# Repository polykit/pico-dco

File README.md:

# Raspberry Pi Pico Polyphonic DCO

This repository contains source code, schematics and PCB for a digitally controlled oscillator (DCO) with up to 6 voices which are driven by a Raspberry Pi Pico. It uses PIO to generate a highly accurate frequency which is controlled by USB or serial MIDI. The analog oscillator part is based on the Juno 106 and generates sawtooth and square wave signal with a 10Vpp amplitude. Amplitude compensation is done by a smoothed PWM signal coming from the Pico.

## Key features

- Digitally controlled analog oscillator using a Raspberry Pi Pico
- Up to six voices
- Voice stacking
- Detuning of voices
- Frequency modulation (FM)
- Separate gate signal
- DIN MIDI serial input
- USB MIDI input
- MIDI pitch bend
- Portamento with adjustable speed

This is how it sounds: [Ramp sample](https://soundcloud.com/polykit/pico-dco-ramp) [Pulse sample](https://soundcloud.com/polykit/pico-dco-pulse) [Polyphonic sample](https://soundcloud.com/polykit/pico-dco-polyphonic)

I use the DCO in my Polykit-6 polyphonic synthesizer, see https://www.youtube.com/watch?v=vj-DSh6yfM0 and https://www.youtube.com/watch?v=go1mErOdtsU

## Schematics and PCB

Gerber files for the PCB can be found [here](kicad/plots).

## Installation (simple)

Press `BOOTSEL` button on the Pico while powering it with USB. Copy file `build/pico-dco.uf2` onto the USB mass storage device.

## Usage

After installing the Pico should register as USB MIDI device. Alternatively serial MIDI input is available. The DCO listens to note on/note off messages on MIDI channel 1. Pitch bend is also supported. Portamento can be enabled by MIDI CC message #65, portamento time can be adjusted by CC message #5.

## Detuning, stacking and FM

The build-in analog-to-digital converter can be used to modulate these parameters. You can add an external control voltage (0-3.3V) to that input pins. These features can be disabled by commenting (`//`) the following lines:

```
#define USE_ADC_STACK_VOICES // gpio 28 (adc 2)
#define USE_ADC_DETUNE       // gpio 27 (adc 1)
#define USE_ADC_FM           // gpio 26 (adc 0)
```

## References

https://blog.thea.codes/the-design-of-the-juno-dco/

https://electricdruid.net/roland-juno-dcos/

https://www.youtube.com/watch?v=yYnQYF_Xa8g

https://github.com/raspberrypi/pico-examples/tree/master/pio/pwm

https://github.com/raspberrypi/pico-examples/tree/master/pio/pio_blink

https://github.com/raspberrypi/pico-examples/tree/master/pwm/hello_pwm

https://qiita.com/jamjam/items/f2fdd5c072ff348fd809

https://github.com/infovore/pico-example-midi

https://learn.sparkfun.com/tutorials/midi-tutorial/all

http://www.music-software-development.com/midi-tutorial.html

http://midi.teragonaudio.com/tech/midispec/run.htm

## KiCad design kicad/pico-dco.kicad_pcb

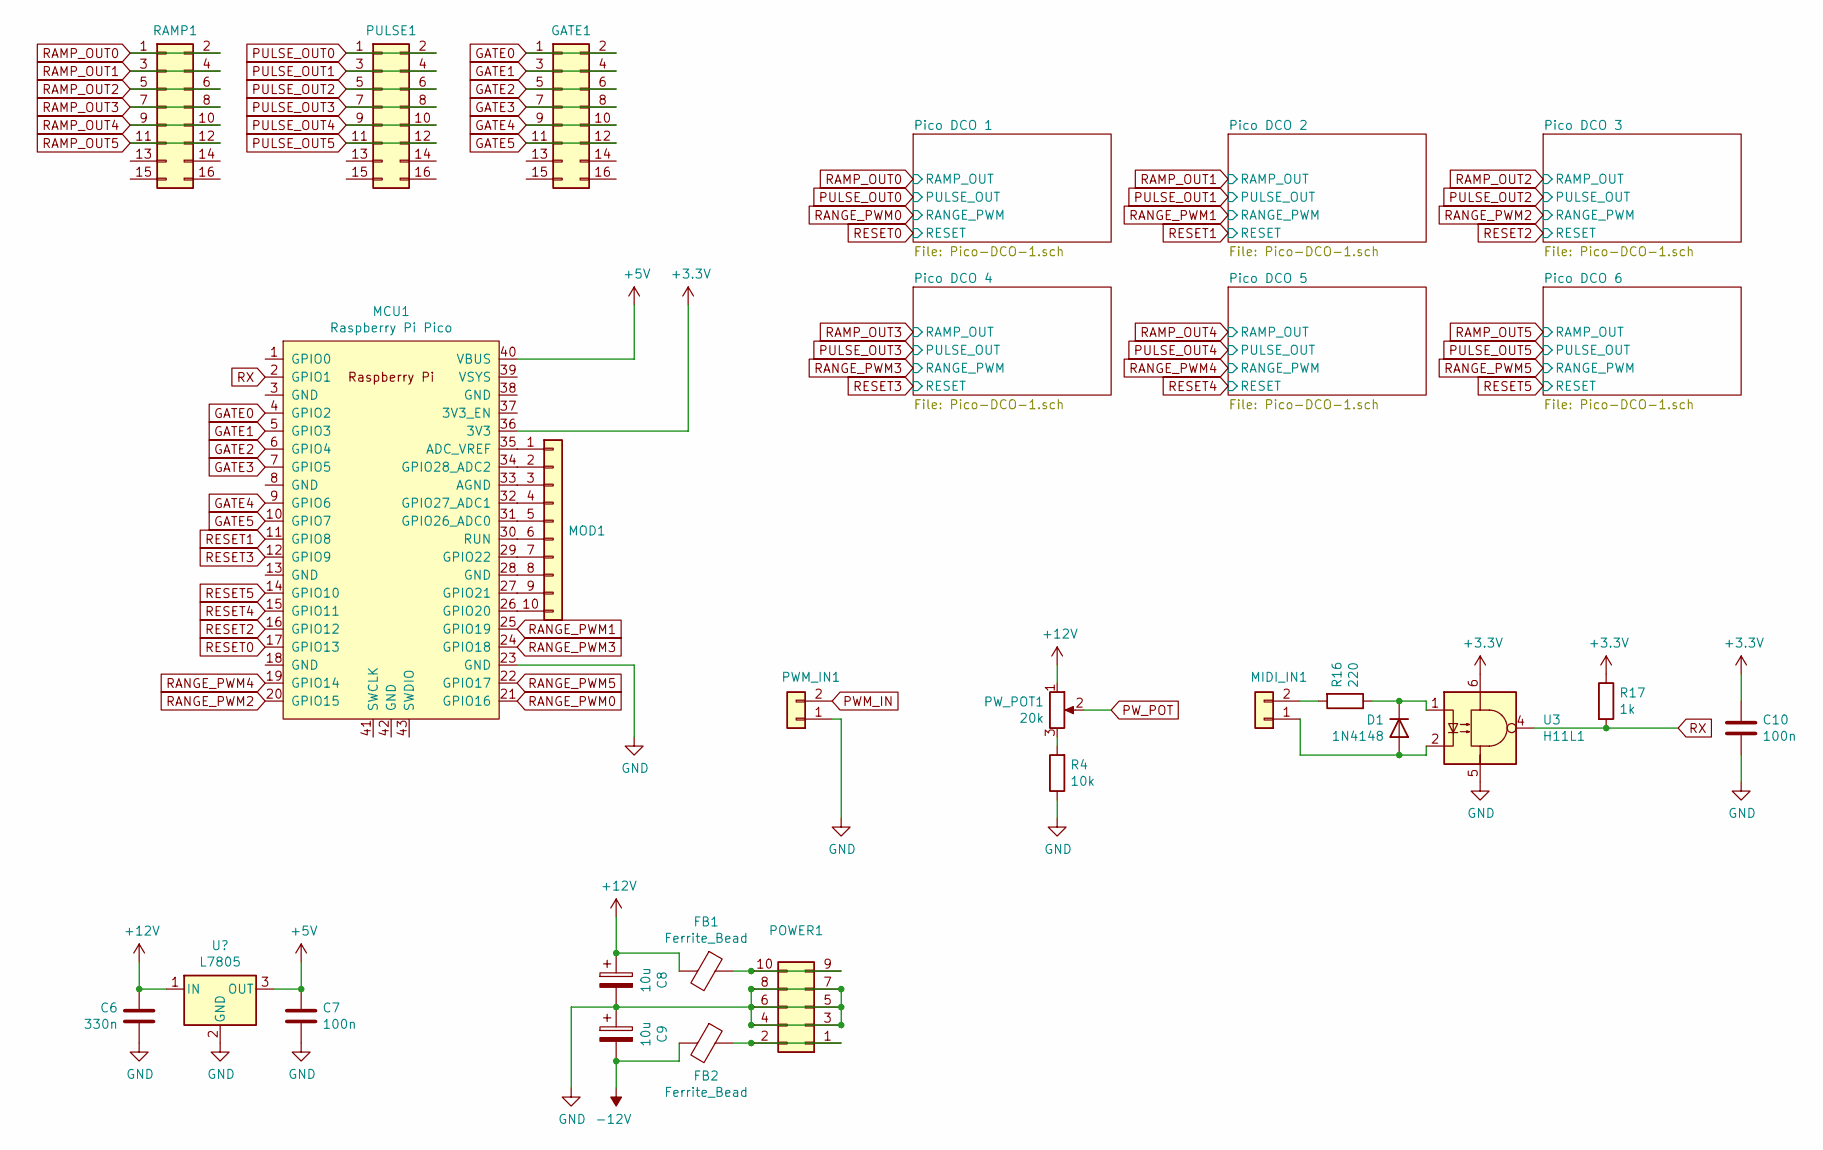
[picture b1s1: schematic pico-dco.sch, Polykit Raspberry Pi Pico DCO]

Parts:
C6: 330n; C_Rect_L7.2mm_W4.5mm_P5.00mm_FKS2_FKP2_MKS2_MKP2
C7, C10: 100n; C_Rect_L7.2mm_W4.5mm_P5.00mm_FKS2_FKP2_MKS2_MKP2
C8, C9: 10u; CP_Radial_D5.0mm_P2.00mm
D1: 1N4148; D_DO-35_SOD27_P7.62mm_Horizontal
FB1, FB2: Ferrite_Bead; R_Axial_DIN0207_L6.3mm_D2.5mm_P10.16mm_Horizontal
GATE1: Conn_02x08_Odd_Even; IDC-Header_2x08_P2.54mm_Vertical
MCU1: Raspberry Pi Pico; RPi_Pico_SMD_TH
MIDI_IN1: Conn_01x02; Molex_KK-254_AE-6410-02A_1x02_P2.54mm_Vertical
MOD1: Conn_01x10; PinHeader_1x10_P2.54mm_Vertical
POWER1: Conn_02x05_Odd_Even; IDC-Header_2x05_P2.54mm_Vertical
PULSE1: Conn_02x08_Odd_Even; IDC-Header_2x08_P2.54mm_Vertical
PWM_IN1: Conn_01x02; Molex_KK-254_AE-6410-02A_1x02_P2.54mm_Vertical
PW_POT1: 20k; Molex_KK-254_AE-6410-03A_1x03_P2.54mm_Vertical
R4: 10k; R_Axial_DIN0207_L6.3mm_D2.5mm_P10.16mm_Horizontal
R16: 220; R_Axial_DIN0207_L6.3mm_D2.5mm_P10.16mm_Horizontal
R17: 1k; R_Axial_DIN0207_L6.3mm_D2.5mm_P10.16mm_Horizontal
RAMP1: Conn_02x08_Odd_Even; IDC-Header_2x08_P2.54mm_Vertical
U3: H11L1; DIP-6_W7.62mm_Socket_LongPads

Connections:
+3V3: C10.1, MCU1.36 (3V3), R17.1, U3.6
+5V: C7.1, MCU1.40 (VBUS); also elsewhere on the board
+12V: C6.2, C8.1, FB1.2, PW_POT1.1; also elsewhere on the board
-12V: C9.2, FB2.2; also elsewhere on the board
GATE0: GATE1.1, GATE1.2, MCU1.4 (GPIO2)
GATE1: GATE1.3, GATE1.4, MCU1.5 (GPIO3)
GATE2: GATE1.5, GATE1.6, MCU1.6 (GPIO4)
GATE3: GATE1.7, GATE1.8, MCU1.7 (GPIO5)
GATE4: GATE1.9, GATE1.10, MCU1.9 (GPIO6)
GATE5: GATE1.11, GATE1.12, MCU1.10 (GPIO7)
GND: C6.1, C7.2, C8.2, C9.1, C10.2, MCU1.23 (GND), POWER1.3, POWER1.4, POWER1.5, POWER1.6, POWER1.7, POWER1.8, PWM_IN1.1, R4.1, U3.5; also elsewhere on the board
unnamed: D1.1 (K), R16.1, U3.1
unnamed: D1.2 (A), MIDI_IN1.1, U3.2
unnamed: FB1.1, POWER1.9, POWER1.10
unnamed: FB2.1, POWER1.1, POWER1.2
unnamed: MCU1.26 (GPIO20), MOD1.10
unnamed: MCU1.27 (GPIO21), MOD1.9
unnamed: MCU1.28 (GND), MOD1.8
unnamed: MCU1.29 (GPIO22), MOD1.7
unnamed: MCU1.30 (RUN), MOD1.6
unnamed: MCU1.31 (GPIO26_ADC0), MOD1.5
unnamed: MCU1.32 (GPIO27_ADC1), MOD1.4
unnamed: MCU1.33 (AGND), MOD1.3
unnamed: MCU1.34 (GPIO28_ADC2), MOD1.2
unnamed: MCU1.35 (ADC_VREF), MOD1.1
unnamed: MIDI_IN1.2, R16.2
unnamed: PW_POT1.3, R4.2
PULSE_OUT0: PULSE1.1, PULSE1.2; also elsewhere on the board
PULSE_OUT1: PULSE1.3, PULSE1.4; also elsewhere on the board
PULSE_OUT2: PULSE1.5, PULSE1.6; also elsewhere on the board
PULSE_OUT3: PULSE1.7, PULSE1.8; also elsewhere on the board
PULSE_OUT4: PULSE1.9, PULSE1.10; also elsewhere on the board
PULSE_OUT5: PULSE1.11, PULSE1.12; also elsewhere on the board
PWM_IN: PWM_IN1.2; also elsewhere on the board
PW_POT: PW_POT1.2; also elsewhere on the board
RAMP_OUT0: RAMP1.1, RAMP1.2; also elsewhere on the board
RAMP_OUT1: RAMP1.3, RAMP1.4; also elsewhere on the board
RAMP_OUT2: RAMP1.5, RAMP1.6; also elsewhere on the board
RAMP_OUT3: RAMP1.7, RAMP1.8; also elsewhere on the board
RAMP_OUT4: RAMP1.9, RAMP1.10; also elsewhere on the board
RAMP_OUT5: RAMP1.11, RAMP1.12; also elsewhere on the board
RANGE_PWM0: MCU1.21 (GPIO16); also elsewhere on the board
RANGE_PWM1: MCU1.25 (GPIO19); also elsewhere on the board
RANGE_PWM2: MCU1.20 (GPIO15); also elsewhere on the board
RANGE_PWM3: MCU1.24 (GPIO18); also elsewhere on the board
RANGE_PWM4: MCU1.19 (GPIO14); also elsewhere on the board
RANGE_PWM5: MCU1.22 (GPIO17); also elsewhere on the board
RESET0: MCU1.17 (GPIO13); also elsewhere on the board
RESET1: MCU1.11 (GPIO8); also elsewhere on the board
RESET2: MCU1.16 (GPIO12); also elsewhere on the board
RESET3: MCU1.12 (GPIO9); also elsewhere on the board
RESET4: MCU1.15 (GPIO11); also elsewhere on the board
RESET5: MCU1.14 (GPIO10); also elsewhere on the board
RX: MCU1.2 (GPIO1), R17.2, U3.4

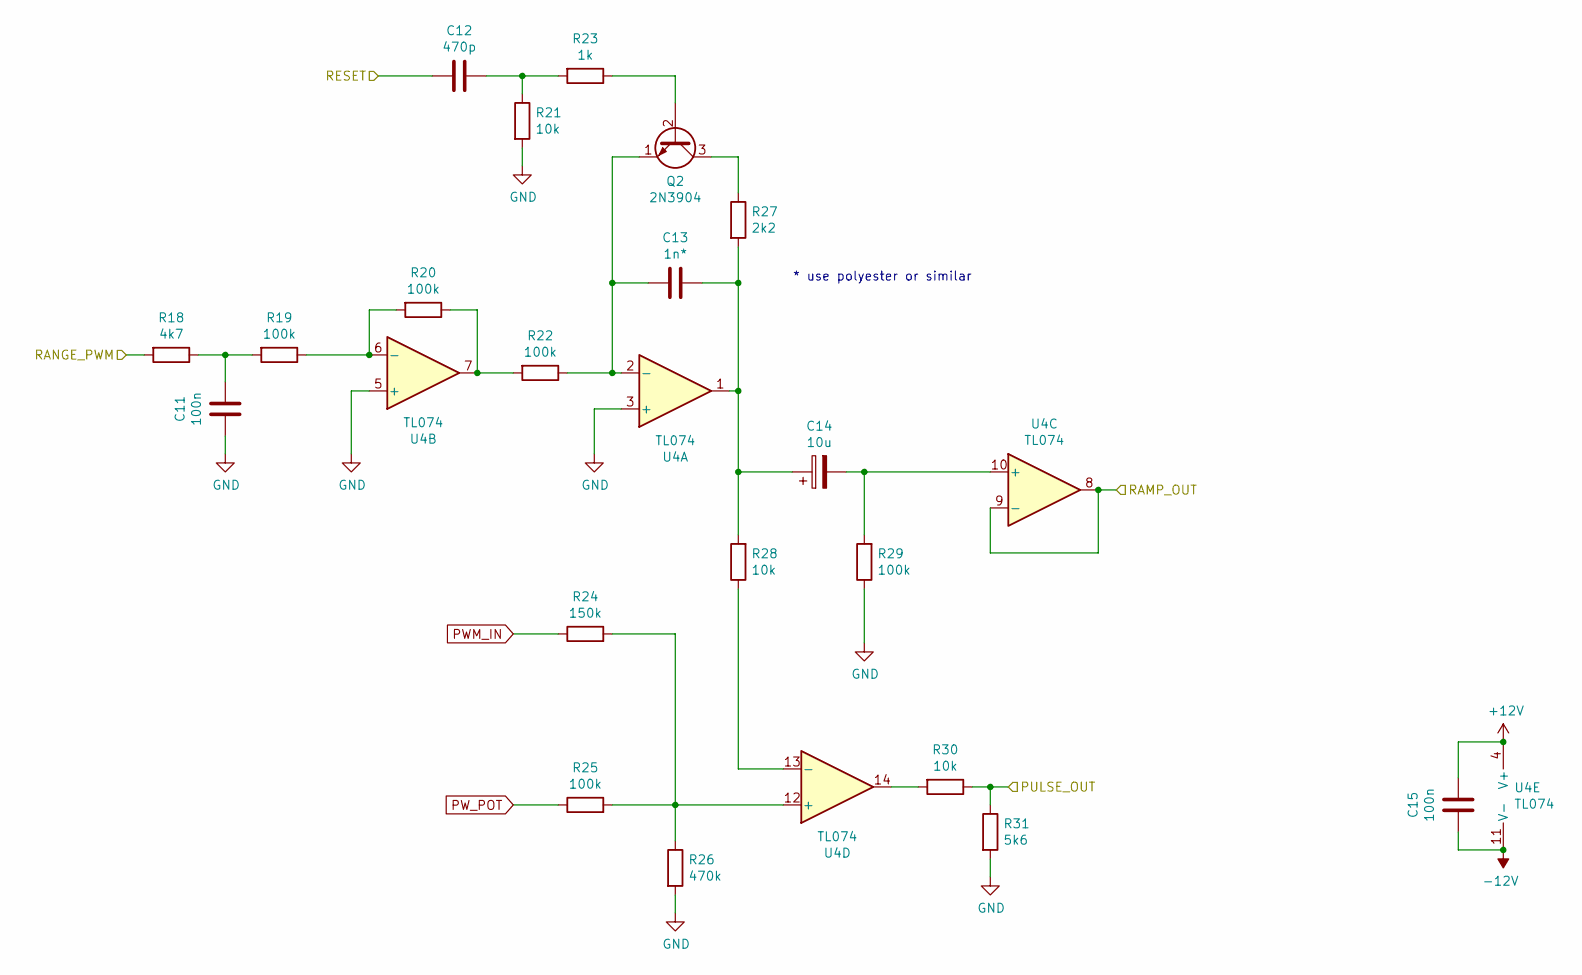
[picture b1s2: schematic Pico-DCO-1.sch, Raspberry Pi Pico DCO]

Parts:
C1, C5: 100n; C_Rect_L7.2mm_W4.5mm_P5.00mm_FKS2_FKP2_MKS2_MKP2
C2: 470p; C_Rect_L7.2mm_W4.5mm_P5.00mm_FKS2_FKP2_MKS2_MKP2
C3: 1n*; C_Rect_L7.2mm_W4.5mm_P5.00mm_FKS2_FKP2_MKS2_MKP2
C4: 10u; CP_Radial_D5.0mm_P2.00mm
Q1: 2N3904; TO-92_Wide
R1: 4k7; R_Axial_DIN0207_L6.3mm_D2.5mm_P10.16mm_Horizontal
R2, R3, R6, R9, R13: 100k; R_Axial_DIN0207_L6.3mm_D2.5mm_P10.16mm_Horizontal
R5, R12, R14: 10k; R_Axial_DIN0207_L6.3mm_D2.5mm_P10.16mm_Horizontal
R7: 1k; R_Axial_DIN0207_L6.3mm_D2.5mm_P10.16mm_Horizontal
R8: 150k; R_Axial_DIN0207_L6.3mm_D2.5mm_P10.16mm_Horizontal
R10: 470k; R_Axial_DIN0207_L6.3mm_D2.5mm_P10.16mm_Horizontal
R11: 2k2; R_Axial_DIN0207_L6.3mm_D2.5mm_P10.16mm_Horizontal
R15: 5k6; R_Axial_DIN0207_L6.3mm_D2.5mm_P10.16mm_Horizontal
U2: TL074; DIP-14_W7.62mm_Socket_LongPads

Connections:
+12V: C5.1, U2.4 (V+); also elsewhere on the board
-12V: C5.2, U2.11 (V-); also elsewhere on the board
GND: C1.2, R5.2, R10.2, R13.1, R15.2, U2.3 (+), U2.5 (+); also elsewhere on the board
unnamed: C1.1, R1.1, R2.2
unnamed: C2.1, R5.1, R7.2
unnamed: C3.1, C4.1, R11.2, R12.2, U2.1
unnamed: C3.2, Q1.1 (E), R6.1, U2.2 (-)
unnamed: C4.2, R13.2, U2.10 (+)
unnamed: Q1.2 (B), R7.1
unnamed: Q1.3 (C), R11.1
unnamed: R2.1, R3.2, U2.6 (-)
unnamed: R3.1, R6.2, U2.7
unnamed: R8.2, R9.2, R10.1, U2.12 (+)
unnamed: R12.1, U2.13 (-)
unnamed: R14.2, U2.14
PULSE_OUT0: R14.1, R15.1; also elsewhere on the board
PWM_IN: R8.1; also elsewhere on the board
PW_POT: R9.1; also elsewhere on the board
RAMP_OUT0: U2.8, U2.9 (-); also elsewhere on the board
RANGE_PWM0: R1.2; also elsewhere on the board
RESET0: C2.2; also elsewhere on the board

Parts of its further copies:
C11, C15, C16, C20, C21, C25, C26, C30, C31, C35: 100n; C_Rect_L7.2mm_W4.5mm_P5.00mm_FKS2_FKP2_MKS2_MKP2
C12, C17, C22, C27, C32: 470p; C_Rect_L7.2mm_W4.5mm_P5.00mm_FKS2_FKP2_MKS2_MKP2
C13, C18, C23, C28, C33: 1n*; C_Rect_L7.2mm_W4.5mm_P5.00mm_FKS2_FKP2_MKS2_MKP2
C14, C19, C24, C29, C34: 10u; CP_Radial_D5.0mm_P2.00mm
Q2, Q3, Q4, Q5, Q6: 2N3904; TO-92_Wide
R18, R32, R46, R60, R74: 4k7; R_Axial_DIN0207_L6.3mm_D2.5mm_P10.16mm_Horizontal
R19, R20, R22, R25, R29, R33, R34, R36, R39, R43, R47, R48, R50, R53, R57, R61, R62, R64, R67, R71, R75, R76, R78, R81, R85: 100k; R_Axial_DIN0207_L6.3mm_D2.5mm_P10.16mm_Horizontal
R21, R28, R30, R35, R42, R44, R49, R56, R58, R63, R70, R72, R77, R84, R86: 10k; R_Axial_DIN0207_L6.3mm_D2.5mm_P10.16mm_Horizontal
R23, R37, R51, R65, R79: 1k; R_Axial_DIN0207_L6.3mm_D2.5mm_P10.16mm_Horizontal
R24, R38, R52, R66, R80: 150k; R_Axial_DIN0207_L6.3mm_D2.5mm_P10.16mm_Horizontal
R26, R40, R54, R68, R82: 470k; R_Axial_DIN0207_L6.3mm_D2.5mm_P10.16mm_Horizontal
R27, R41, R55, R69, R83: 2k2; R_Axial_DIN0207_L6.3mm_D2.5mm_P10.16mm_Horizontal
R31, R45, R59, R73, R87: 5k6; R_Axial_DIN0207_L6.3mm_D2.5mm_P10.16mm_Horizontal
U4, U5, U6, U7, U8: TL074; DIP-14_W7.62mm_Socket_LongPads

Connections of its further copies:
+12V: C15.1, C20.1, C25.1, C30.1, C35.1, U4.4 (V+), U5.4 (V+), U6.4 (V+), U7.4 (V+), U8.4 (V+); also elsewhere on the board
-12V: C15.2, C20.2, C25.2, C30.2, C35.2, U4.11 (V-), U5.11 (V-), U6.11 (V-), U7.11 (V-), U8.11 (V-); also elsewhere on the board
GND: C11.2, C16.2, C21.2, C26.2, C31.2, R21.2, R26.2, R29.1, R31.2, R35.2, R40.2, R43.1, R45.2, R49.2, R54.2, R57.1, R59.2, R63.2, R68.2, R71.1, R73.2, R77.2, R82.2, R85.1, R87.2, U4.3 (+), U4.5 (+), U5.3 (+), U5.5 (+), U6.3 (+), U6.5 (+), U7.3 (+), U7.5 (+), U8.3 (+), U8.5 (+); also elsewhere on the board
unnamed: C11.1, R18.1, R19.2
unnamed: C12.1, R21.1, R23.2
unnamed: C13.1, C14.1, R27.2, R28.2, U4.1
unnamed: C13.2, Q2.1 (E), R22.1, U4.2 (-)
unnamed: C14.2, R29.2, U4.10 (+)
unnamed: C16.1, R32.1, R33.2
unnamed: C17.1, R35.1, R37.2
unnamed: C18.1, C19.1, R41.2, R42.2, U5.1
unnamed: C18.2, Q3.1 (E), R36.1, U5.2 (-)
unnamed: C19.2, R43.2, U5.10 (+)
unnamed: C21.1, R46.1, R47.2
unnamed: C22.1, R49.1, R51.2
unnamed: C23.1, C24.1, R55.2, R56.2, U6.1
unnamed: C23.2, Q4.1 (E), R50.1, U6.2 (-)
unnamed: C24.2, R57.2, U6.10 (+)
unnamed: C26.1, R60.1, R61.2
unnamed: C27.1, R63.1, R65.2
unnamed: C28.1, C29.1, R69.2, R70.2, U7.1
unnamed: C28.2, Q5.1 (E), R64.1, U7.2 (-)
unnamed: C29.2, R71.2, U7.10 (+)
unnamed: C31.1, R74.1, R75.2
unnamed: C32.1, R77.1, R79.2
unnamed: C33.1, C34.1, R83.2, R84.2, U8.1
unnamed: C33.2, Q6.1 (E), R78.1, U8.2 (-)
unnamed: C34.2, R85.2, U8.10 (+)
unnamed: Q2.2 (B), R23.1
unnamed: Q2.3 (C), R27.1
unnamed: Q3.2 (B), R37.1
unnamed: Q3.3 (C), R41.1
unnamed: Q4.2 (B), R51.1
unnamed: Q4.3 (C), R55.1
unnamed: Q5.2 (B), R65.1
unnamed: Q5.3 (C), R69.1
unnamed: Q6.2 (B), R79.1
unnamed: Q6.3 (C), R83.1
unnamed: R19.1, R20.2, U4.6 (-)
unnamed: R20.1, R22.2, U4.7
unnamed: R24.2, R25.2, R26.1, U4.12 (+)
unnamed: R28.1, U4.13 (-)
unnamed: R30.2, U4.14
unnamed: R33.1, R34.2, U5.6 (-)
unnamed: R34.1, R36.2, U5.7
unnamed: R38.2, R39.2, R40.1, U5.12 (+)
unnamed: R42.1, U5.13 (-)
unnamed: R44.2, U5.14
unnamed: R47.1, R48.2, U6.6 (-)
unnamed: R48.1, R50.2, U6.7
unnamed: R52.2, R53.2, R54.1, U6.12 (+)
unnamed: R56.1, U6.13 (-)
unnamed: R58.2, U6.14
unnamed: R61.1, R62.2, U7.6 (-)
unnamed: R62.1, R64.2, U7.7
unnamed: R66.2, R67.2, R68.1, U7.12 (+)
unnamed: R70.1, U7.13 (-)
unnamed: R72.2, U7.14
unnamed: R75.1, R76.2, U8.6 (-)
unnamed: R76.1, R78.2, U8.7
unnamed: R80.2, R81.2, R82.1, U8.12 (+)
unnamed: R84.1, U8.13 (-)
unnamed: R86.2, U8.14
PULSE_OUT1: R30.1, R31.1; also elsewhere on the board
PULSE_OUT2: R44.1, R45.1; also elsewhere on the board
PULSE_OUT3: R58.1, R59.1; also elsewhere on the board
PULSE_OUT4: R72.1, R73.1; also elsewhere on the board
PULSE_OUT5: R86.1, R87.1; also elsewhere on the board
PWM_IN: R24.1, R38.1, R52.1, R66.1, R80.1; also elsewhere on the board
PW_POT: R25.1, R39.1, R53.1, R67.1, R81.1; also elsewhere on the board
RAMP_OUT1: U4.8, U4.9 (-); also elsewhere on the board
RAMP_OUT2: U5.8, U5.9 (-); also elsewhere on the board
RAMP_OUT3: U6.8, U6.9 (-); also elsewhere on the board
RAMP_OUT4: U7.8, U7.9 (-); also elsewhere on the board
RAMP_OUT5: U8.8, U8.9 (-); also elsewhere on the board
RANGE_PWM1: R18.2; also elsewhere on the board
RANGE_PWM2: R32.2; also elsewhere on the board
RANGE_PWM3: R46.2; also elsewhere on the board
RANGE_PWM4: R60.2; also elsewhere on the board
RANGE_PWM5: R74.2; also elsewhere on the board
RESET1: C12.2; also elsewhere on the board
RESET2: C17.2; also elsewhere on the board
RESET3: C22.2; also elsewhere on the board
RESET4: C27.2; also elsewhere on the board
RESET5: C32.2; also elsewhere on the board

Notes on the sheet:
* use polyester or similar

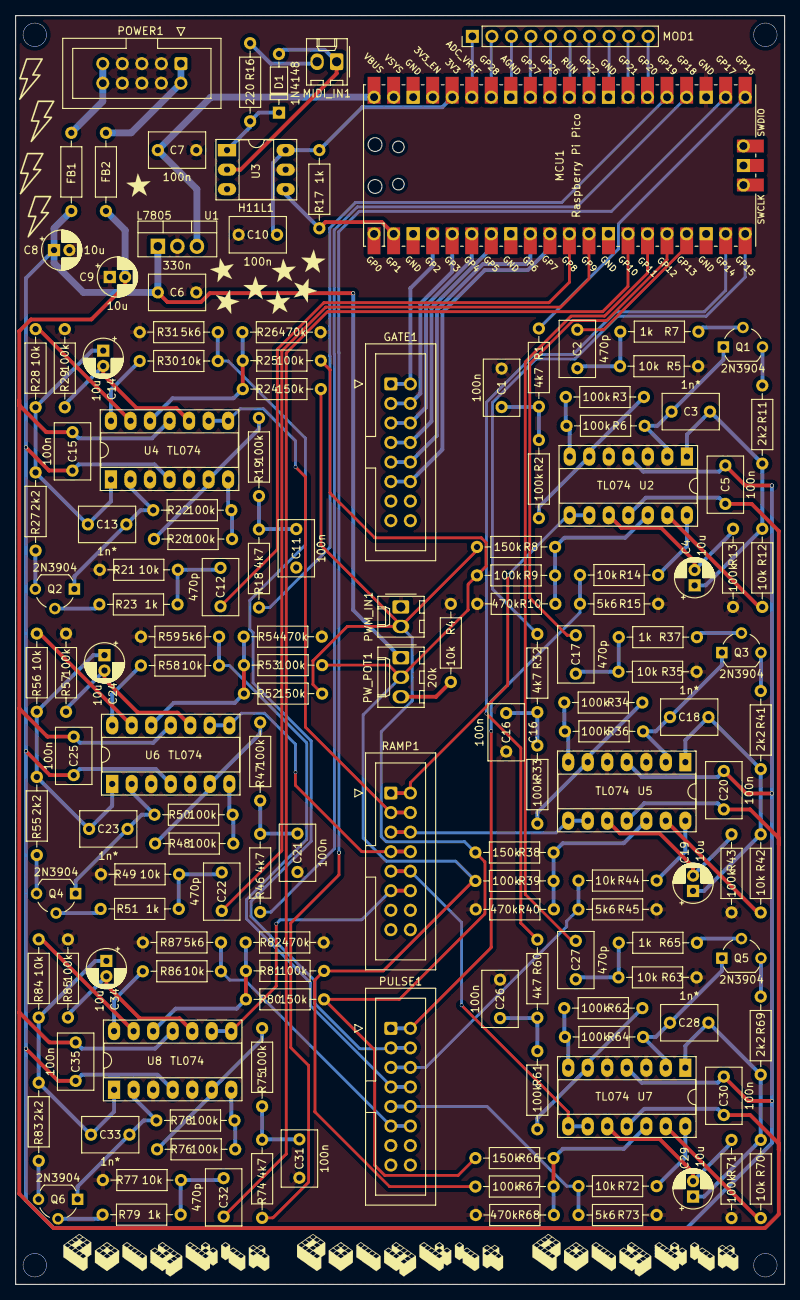
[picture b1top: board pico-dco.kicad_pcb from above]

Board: 2 copper layers, 100.0 x 165.0 mm, 148 parts (0 on the bottom side), 126 nets.

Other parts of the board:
U1: L7805; TO-220-3_Vertical

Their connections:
+5V: U1.3; also elsewhere on the board
+12V: U1.1; also elsewhere on the board
GND: U1.2; also elsewhere on the board

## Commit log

2021-04-23 Initial import
2021-05-22 Add 6 voices and serial midi to kicad schematics/PCB
2021-05-22 Add code for serial midi
2021-05-22 Update silk screen
2021-05-23 Changed 5V regulator to L7805
2021-05-23 Add polyphony, update readme
2021-06-15 Add proper voice assignment
2021-06-26 Fix midi running state, add pitch bend
2021-06-29 Fix usb midi
2021-10-30 Fix next free voice
2021-10-30 Optimize pitch_bend_task
2021-11-03 Allow stacking of voices
2021-12-12 Add voice stacking/detuning on adc readings
2022-04-30 Add portamento
2022-04-30 Changes readme
2022-08-04 Added support for linear FM on GPIO26 (ADC0)
2022-08-06 Removed blocking functions from MIDI function; removed conditional execution of synthesis code
2022-08-06 Seperated MIDI note and gate control
2022-08-07 Changed voice allocation to use gate information
2022-08-07 Fixed voice gate when MIDI note on is received
2022-11-07 Add adc section to readme
2022-11-07 Add image to readme
2022-11-07 Fix typo
2023-03-25 Fix usb midi channels #4
2023-03-25 Update build file
